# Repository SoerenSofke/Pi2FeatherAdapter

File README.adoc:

= FeatherWing Adapter for Raspberry Pi

### Rendering of Pi-to-Feather Adapter
image::assets/rendering.jpg[]

### Schematic
image::assets/schematic.svg[]

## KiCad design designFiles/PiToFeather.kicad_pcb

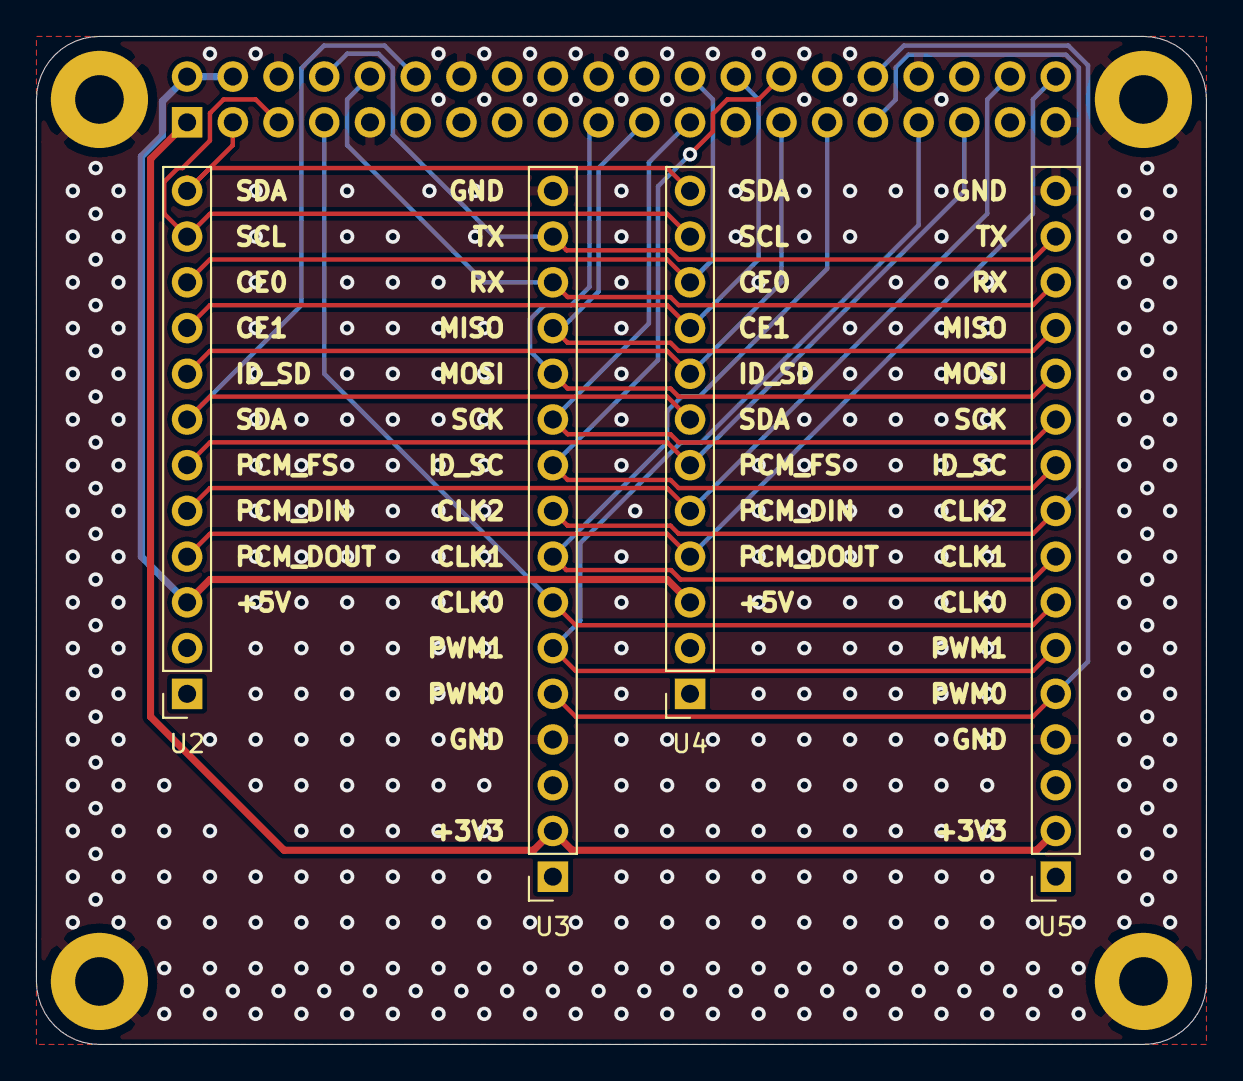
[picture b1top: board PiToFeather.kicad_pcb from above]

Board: 2 copper layers, 65.0 x 56.0 mm, 9 parts (1 on the bottom side), 23 nets.

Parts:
H1, H2, H3, H4: MountingHole_Pad; MountingHole_2.7mm_M2.5_Pad
U1: piHeader; PinSocket_2x20_P2.54mm_Vertical
U2, U4: featherHeader_12pin; PinSocket_1x12_P2.54mm_Vertical
U3, U5: featherHeader_16pin; PinSocket_1x16_P2.54mm_Vertical

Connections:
+3V3: U1.1, U1.17, U3.2, U5.2
+5V: U1.2, U1.4, U2.3, U4.3
CE0: U1.24, U2.10, U4.10
CE1: U1.26, U2.9, U4.9
CLK0: U1.7, U3.7, U5.7
CLK1: U1.29, U3.8, U5.8
CLK2: U1.31, U3.9, U5.9
GND: H1.1, H2.1, H3.1, H4.1, U1.6, U1.9, U1.14, U1.20, U1.25, U1.30, U1.34, U1.39, U3.4, U3.16, U5.4, U5.16
ID_SC: U1.28, U3.10, U5.10
ID_SD: U1.27, U2.8, U4.8
MISO: U1.21, U3.13, U5.13
MOSI: U1.19, U3.12, U5.12
PCM_CLK: U1.12, U2.7, U4.7
PCM_DIN: U1.38, U2.5, U4.5
PCM_DOUT: U1.40, U2.4, U4.4
PCM_FS: U1.35, U2.6, U4.6
PWM0: U1.32, U3.5, U5.5
PWM1: U1.33, U3.6, U5.6
RX: U1.10, U3.14, U5.14
SCK: U1.23, U3.11, U5.11
SCL: U1.5, U2.11, U4.11
SDA: U1.3, U2.12, U4.12
TX: U1.8, U3.15, U5.15

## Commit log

2020-08-01 Schematic and initial layout
2020-08-03 add second fetherwing pinout
2020-08-03 Start layout incl. board outline
2020-08-03 Refinements in routing
2020-08-03 minor improvemnts in routing
2020-08-04 mounting holes with pads added
2020-08-04 power with increaseds track width
2020-08-04 stitching vias added
2020-08-04 design rule check hints integrated
2020-08-17 Change of RX and TX
2020-08-17 export of gerber + drill (files)
2020-08-17 Project updated
2020-08-18 typo corected
2020-09-15 Python application to show clock on display
    Fixes soerensofke/Pi2FeatherAdapter#1
2020-09-15 Initial commit of README
2020-09-15 Definition of AsciiDoc-plugin for Gitpod
2020-09-15 remove python code listing, not supported
    AsciiDoc include is not supported in GitHub
2020-09-15 schematic integrated
    Fixes soerensofke/Pi2FeatherAdapter#3
2020-09-15 Form in schematic filled
